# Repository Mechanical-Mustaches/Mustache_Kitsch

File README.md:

# Mustache_Kitsch
things like mustache badges and other cool mustache related gear

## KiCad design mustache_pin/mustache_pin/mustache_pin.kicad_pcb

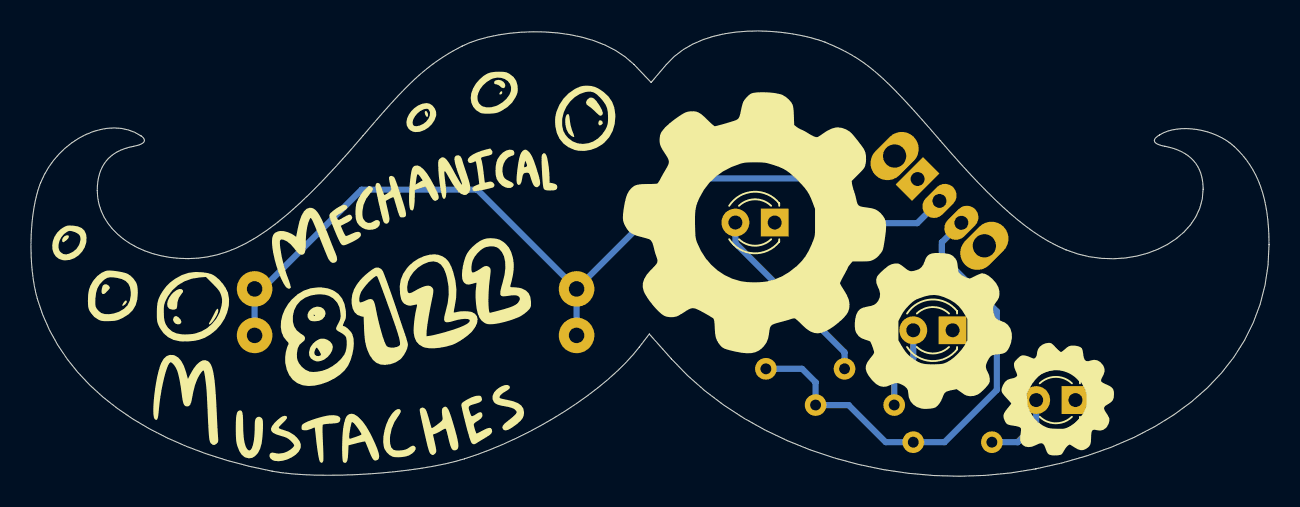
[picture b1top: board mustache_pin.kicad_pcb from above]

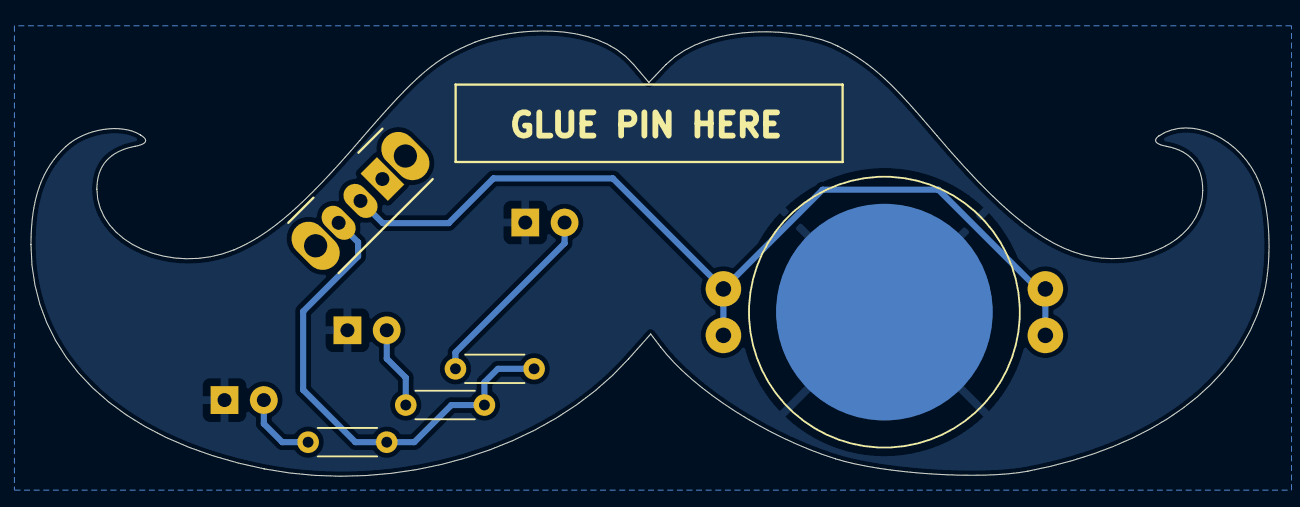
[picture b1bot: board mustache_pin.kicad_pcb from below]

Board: 2 copper layers, 80.0 x 28.8 mm, 8 parts (5 on the bottom side), 6 nets.

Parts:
BT1: Battery_Cell; Battery_Contact_CR2032_CoinCell
D1, D3: LED; LED_D3.0mm
De: LED; LED_D3.0mm
R1, R2, R3: 220R; R_Axial_DIN0204_L3.6mm_D1.6mm_P5.08mm_Horizontal
SW1: SW_SPDT; SW_CuK_OS102011MA1QN1_SPDT_Angled

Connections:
GND: BT1.2 (-), D1.1 (K), D3.1 (K), De.1 (K)
unnamed: BT1.1 (+), SW1.2 (B)
unnamed: D1.2 (A), R1.1
unnamed: De.2 (A), R2.1
unnamed: D3.2 (A), R3.1
unnamed: R1.2, R2.2, R3.2, SW1.3 (C)

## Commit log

2022-10-07 add mustache pin :{D
2022-10-07 silkscreens are weird
2022-10-07 commit pt2
